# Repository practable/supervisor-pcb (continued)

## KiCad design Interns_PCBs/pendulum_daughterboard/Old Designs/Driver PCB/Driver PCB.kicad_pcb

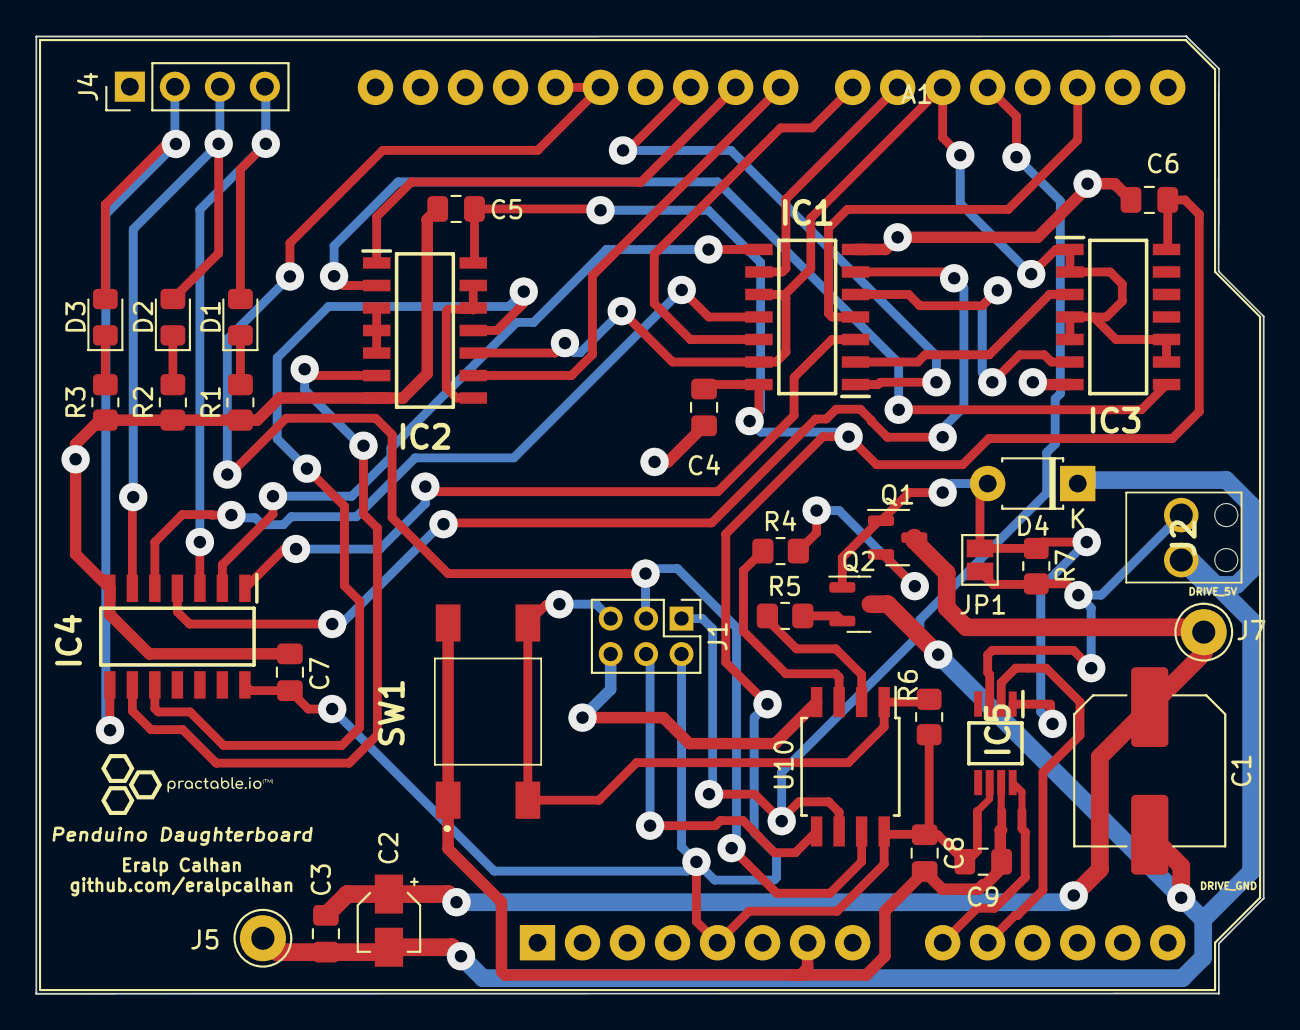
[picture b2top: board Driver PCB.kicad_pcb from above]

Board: 2 copper layers, 69.2 x 54.0 mm, 42 parts (0 on the bottom side), 46 nets.

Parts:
A1: Infineon Motor Shield MOD; Infineon Motor Sheild hiddenPins
C1: 470u; C_Elec_8x10.2
C2: 10u; CP_Elec_3x5.3
C3: 0.1u; C_0805_2012Metric_Pad1.18x1.45mm_HandSolder
C4, C5, C6, C7, C8: 100nF; C_0805_2012Metric_Pad1.18x1.45mm_HandSolder
C9: 0.1uF; C_0805_2012Metric_Pad1.18x1.45mm_HandSolder
D1, D2, D3: LED; LED_0805_2012Metric_Pad1.15x1.40mm_HandSolder
D4: 1N4002; D_T-1_P5.08mm_Horizontal
IC1: AND GATES; SOIC127P600X175-14N
IC2: NAND (Used as AND); SOIC127P600X175-14N
IC3: NAND (Used as Inverter); SOIC127P600X175-14N
IC4: OR; SOIC127P600X175-14N
IC5: MAX9928FAUA+; SOP65P490X110-8N
J1: AVR-ISP-6; PinHeader_2x03_P2.00mm_Vertical
J2: Coil; RSPROPenduinoTerminal
J4: Conn_01x04; PinHeader_1x04_P2.54mm_Vertical
J5: DRIVE_GND; Pin_D1.3mm_L11.0mm
J7: DRIVE_5V_IN; Pin_D1.3mm_L11.0mm
JP1: Shunt Bypass; SolderJumper-2_P1.3mm_Open_Pad1.0x1.5mm
NT1, NT2, NT3, NT4, NT5, NT6: NetTie_2; NetTie-2_SMD_Pad0.5mm
Q1: BC557; SOT-23
Q2: BC547; SOT-23
R1, R2, R3: 120; R_0805_2012Metric_Pad1.20x1.40mm_HandSolder
R4, R5: 2k2; R_0805_2012Metric_Pad1.20x1.40mm_HandSolder
R6: 100k; R_0805_2012Metric_Pad1.20x1.40mm_HandSolder
R7: 10R; R_0805_2012Metric_Pad1.20x1.40mm_HandSolder
SW1: SW_Push; 13019319
U10: ATtiny85-20S; SOIC-8W_5.3x5.3mm_P1.27mm

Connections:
AND_STU_LED_1: IC1.8 (3Y), IC4.2 (B1)
AND_STU_LED_2: IC1.11 (4Y), IC4.5 (B2)
AND_STU_LED_3: IC2.11 (Y4), IC4.10 (B3)
AND_SUP_LED_1: IC1.3 (1Y), IC4.1 (A1)
AND_SUP_LED_2: IC1.6 (2Y), IC4.4 (A2)
AND_SUP_LED_3: IC2.6 (Y2), IC4.9 (A3)
CURRENT_SENSE_OUT: A1.9 (IS_1), NT6.2
CURRENT_SIGN_OUT: A1.10 (IS_2), NT3.1
DRIVE_5V: C1.1, C2.1, C3.1, J7.1, Q1.3 (E)
DRIVE_GND: C1.2, C2.2, C3.2, D4.1 (A), J2.1, J5.1, Q2.3 (E)
DRIVE_INPUT: A1.27 (INH_1), A1.28 (INH_2), J1.3 (SCK), U10.7 (PB2)
DRIVE_MCU: R4.2, U10.3 (XTAL2/PB4)
D_5V: A1.5 (5V), C4.1, C5.1, C6.1, C7.1, C8.1, C9.1, IC1.14 (VCC), IC2.14 (VCC), IC3.14 (VCC), IC4.14 (VCC), J1.2 (VCC), NT1.2, R6.2, U10.8 (VCC)
D_GND: A1.7 (GND), C4.2, C5.2, C6.2, C7.2, C8.2, C9.2, IC1.7 (GND), IC2.7 (GND), IC3.7 (GND), IC4.7 (GND), J1.6 (GND), J4.1, NT2.2, R1.1, R2.1, R3.1, SW1.1, U10.4 (GND)
INV_1: IC1.2 (1B), IC3.3 (Y1)
INV_2: IC1.5 (2B), IC3.6 (Y2)
INV_3: IC2.2 (B1), IC3.8 (Y3)
LOAD_INPUT: A1.19 (D4), J1.1 (MISO), U10.6 (PB1)
LOAD_MCU: R5.2, U10.2 (XTAL1/PB3)
unnamed: D1.1 (K), R1.2
unnamed: D2.1 (K), R2.2
unnamed: D3.1 (K), R3.2
unnamed: D4.2 (K), JP1.1 (A), NT5.1, Q1.1 (C), Q2.1 (C), R7.1
unnamed: IC2.3 (Y1), IC2.4 (A2), IC2.5 (B2)
unnamed: IC2.8 (Y3), IC2.12 (A4), IC2.13 (B4)
unnamed: IC5.1 (RS-), NT5.2
unnamed: IC5.2 (SIGN), NT3.2
unnamed: IC5.3 (RS+), NT4.2
unnamed: IC5.6 (VCC), NT1.1
unnamed: IC5.7 (GND), NT2.1
unnamed: IC5.8 (OUT), NT6.1
unnamed: J1.4 (MOSI), U10.5 (AREF/PB0)
unnamed: J1.5 (~RST), R6.1, SW1.2, U10.1 (~RESET/PB5)
unnamed: J2.2, JP1.2 (B), NT4.1, R7.2
unnamed: Q1.2 (B), R4.1
unnamed: Q2.2 (B), R5.1
OR_OUT_1: D1.2 (A), IC4.3 (Y1), J4.4
OR_OUT_2: D2.2 (A), IC4.6 (Y2), J4.3
OR_OUT_3: D3.2 (A), IC4.8 (Y3), J4.2
STUDENT_ENABLE: A1.20 (D5), IC1.10 (3B), IC1.13 (4B), IC2.10 (B3), IC3.1 (A1), IC3.2 (B1), IC3.4 (A2), IC3.5 (B2), IC3.9 (A3), IC3.10 (B3)
STU_LED_1: A1.21 (D6), IC1.9 (3A)
STU_LED_2: A1.22 (D7), IC1.12 (4A)
STU_LED_3: A1.23 (D8), IC2.9 (A3)
SUP_LED_1: A1.25 (D10), IC1.1 (1A)
SUP_LED_2: A1.17 (D2), IC1.4 (2A)
SUP_LED_3: A1.24 (D9), IC2.1 (A1)

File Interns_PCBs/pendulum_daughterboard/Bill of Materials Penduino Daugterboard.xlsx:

Component Name | Component ID | quantity | Value | Description | Vendor | Part Number | Link | Unit Price (ex. VAT) | Requisition Number | Ordered | Q Boards | Total Price
logic IC AND Gate | IC1 | 1 | NA |  | Farnell | MC74HC08ADG | https://uk.farnell.com/on-semiconductor/mc74hc08adg/ic-74hc-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 | 0.63 |  | No | 42 | 26.46
Logic IC OR Gate | IC2 | 1 | NA |  | Farnell | MC74HC32ADG | https://uk.farnell.com/on-semiconductor/mc74hc32adg/ic-74hc-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 | 0.56999999999999995 |  | No | 42 | 23.939999999999998
Logic IC NAND Gate | IC3 | 1 | NA |  | Farnell | MC74ACT00DG | https://uk.farnell.com/on-semiconductor/mc74act00dg/ic-quad-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 | 0.68 |  | No | 42 | 28.560000000000002
Logic IC NAND Gate | IC4 | 1 | NA |  | Farnell | MC74ACT00DG | https://uk.farnell.com/on-semiconductor/mc74act00dg/ic-quad-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 | 0.68 |  | No | 42 | 28.560000000000002
Current Sense Amplifier | IC5 | 1 | NA | Current Sense Amplifier | Farnell | MAX9928FAUA+ | https://uk.farnell.com/maxim-integrated-products/max9928faua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 | 1.88 |  | Yes | 42 | 78.959999999999994
LED Green | D1 | 1 | NA | Green LED | Farnell | MP008291 | https://uk.farnell.com/multicomp-pro/mp008291/led-green-70mc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 | 0.11 |  | No | 42 | 4.62
LED Orange | D2 | 1 | NA | Orange LED | Farnell | KPT-2012SECK | https://uk.farnell.com/kingbright/kpt-2012seck/led-orange-08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 | 0.12 |  | No | 42 | 5.04
LED Red | D3 | 1 | NA | Red LED | Farnell | MP008293 | https://uk.farnell.com/multicomp-pro/mp008293/led-red-220mcd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 | 0.1 |  | No | 42 | 4.2
Diode | D4 | 1 | NA |  | Farnell | 1N4002 | https://uk.farnell.com/multicomp/1n4002-t/diode-standard-rec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 | 0.13 |  | No | 42 | 5.46
Resistance | R1, R2, R3 | 3 | 120 | 120 OHM resistor for the LED circuit | Farnell | ERA6AEB121V | https://uk.farnell.com/panasonic/era6aeb121v/res-120r-0-125w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 | 0.27 |  | No | 42 | 34.020000000000003
Resistance | R4, R5 | 2 | 2k2 |  | Farnell | 1614917-1 | https://uk.farnell.com/neohm-te-connectivity/1614917-1/res-2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 | 0.17 |  | No | 42 | 14.280000000000001
Resistance | R6 | 1 | 100k |  | Farnell | RS73F2ATTD1003B | https://uk.farnell.com/koa-speer-electronics/rs73f2attd1003b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 | 0.18 |  | No | 42 | 7.56
Resistance | R7 | 1 | 10 |  | Farnell | 2-1614883-3 | https://uk.farnell.com/neohm-te-connectivity/2-1614883-3/res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 | 0.17 |  | No | 42 | 7.1400000000000006
Capacitor | C1 | 1 | 460u |  | Farnell | EEE1CA471UAP | https://uk.farnell.com/panasonic/eee1ca471uap/cap-470-f-16v-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 | 0.69 |  | No | 42 | 28.979999999999997
Capacitor | C2 | 1 | 10u |  | Farnell | AVE106M16A12T-F | https://uk.farnell.com/cornell-dubilier/ave106m16a12t-f/alum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 | 0.45 |  | No | 42 | 18.900000000000002
Capacitor | C3, C4, C5, C6,C7, C8, C9 | 7 | 100nF |  | Farnell | C0805C104K3RACTU | https://uk.farnell.com/kemet/c0805c104k3ractu/cap-0-1-f-25v-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 | 0.06 |  | No | 42 | 17.64
BJT PNP Transistor | Q1 | 1 | NA |  | Farnell | BC807-40LT1G | https://uk.farnell.com/on-semiconductor/bc807-40lt1g/trans-p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 | 0.18 |  | No | 42 | 7.56
BJT NPN Transistor | Q2 | 1 | NA |  | Farnell | BC817,215 | https://uk.farnell.com/nexperia/bc817-215/transistor-npn-45v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 | 0.25 |  | No | 42 | 10.5
AVR Programming Pin | J1 | 1 | NA |  | Farnell | 826925-3 | https://uk.farnell.com/amp-te-connectivity/826925-3/header-t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 | 0.69 |  | No | 42 | 28.979999999999997
2 way PCB terminal | J2 | 1 | NA |  | RS Components | 790-1098 | https://uk.rs-online.com/web/p/pcb-terminal-blocks/7901098 | 0.51200000000000001 |  | No | 42 | 21.504000000000001
4 way PCB terminal | J4 | 1 | NA |  | RS Components | 790-1102 | https://uk.rs-online.com/web/p/pcb-terminal-blocks/7901102 | 0.92400000000000004 |  | No | 42 | 38.808
Tactile Switch | SW1 | 1 | NA | Push Button | Farnell | 1301.9318.24 | https://uk.farnell.com/schurter/1301-9318-24/tactile-switch-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 | 0.42 |  | No | 42 | 17.64
ATtiny85-20S | U1 | 1 | NA | Microcontroller | RS Components | ATTINY85-20SF | https://uk.rs-online.com/web/p/microcontrollers/1717852/?rel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 | 1.8140000000000001 |  | No | 42 | 76.188000000000002
 |  |  |  |  |  |  |  |  |  |  |  | 535.5

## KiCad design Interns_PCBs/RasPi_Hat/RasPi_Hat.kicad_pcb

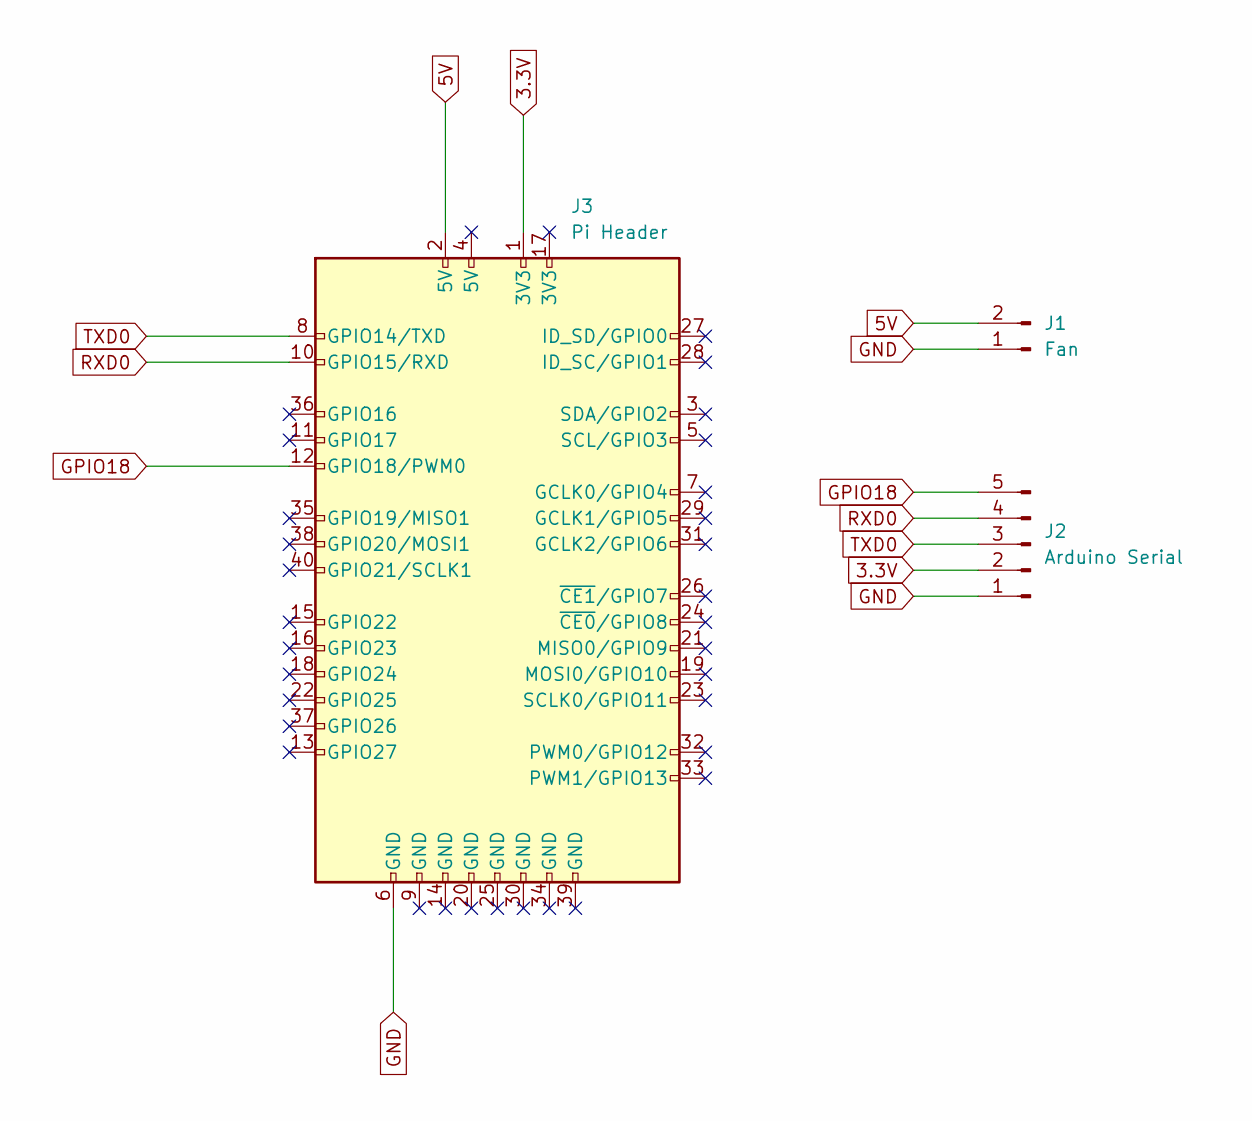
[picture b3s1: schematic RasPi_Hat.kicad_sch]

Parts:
J1: Fan; Molex_KK-254_AE-6410-02A_1x02_P2.54mm_Vertical
J2: Arduino Serial; Molex_KK-254_AE-6410-05A_1x05_P2.54mm_Vertical
J3: Pi Header; PinHeader_2x20_P2.54mm_Vertical

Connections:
3.3V: J2.2, J3.1 (3V3)
5V: J1.2, J3.2 (5V)
GND: J1.1, J2.1, J3.6 (GND)
GPIO18: J2.5, J3.12 (GPIO18/PWM0)
RXD0: J2.4, J3.10 (GPIO15/RXD)
TXD0: J2.3, J3.8 (GPIO14/TXD)

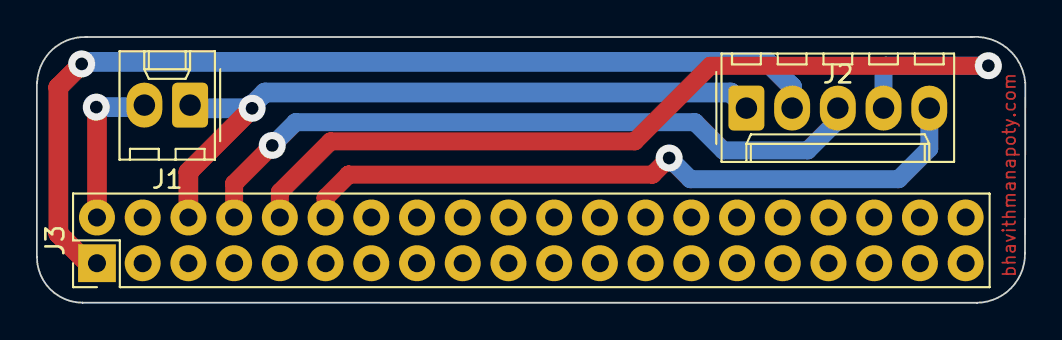
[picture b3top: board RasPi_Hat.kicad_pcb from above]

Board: 2 copper layers, 54.9 x 14.8 mm, 3 parts (0 on the bottom side), 6 nets.

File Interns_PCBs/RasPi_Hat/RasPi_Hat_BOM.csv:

"Id";"Designator";"Package";"Quantity";"Designation";"Supplier and ref";
1;"J2";"Molex_KK-254_AE-6410-05A_1x05_P2.54mm_Vertical";1;"Arduino Serial";;;
2;"J1";"Molex_KK-254_AE-6410-02A_1x02_P2.54mm_Vertical";1;"Fan";;;
3;"J3";"PinHeader_2x20_P2.54mm_Vertical";1;"Pi Header";;;

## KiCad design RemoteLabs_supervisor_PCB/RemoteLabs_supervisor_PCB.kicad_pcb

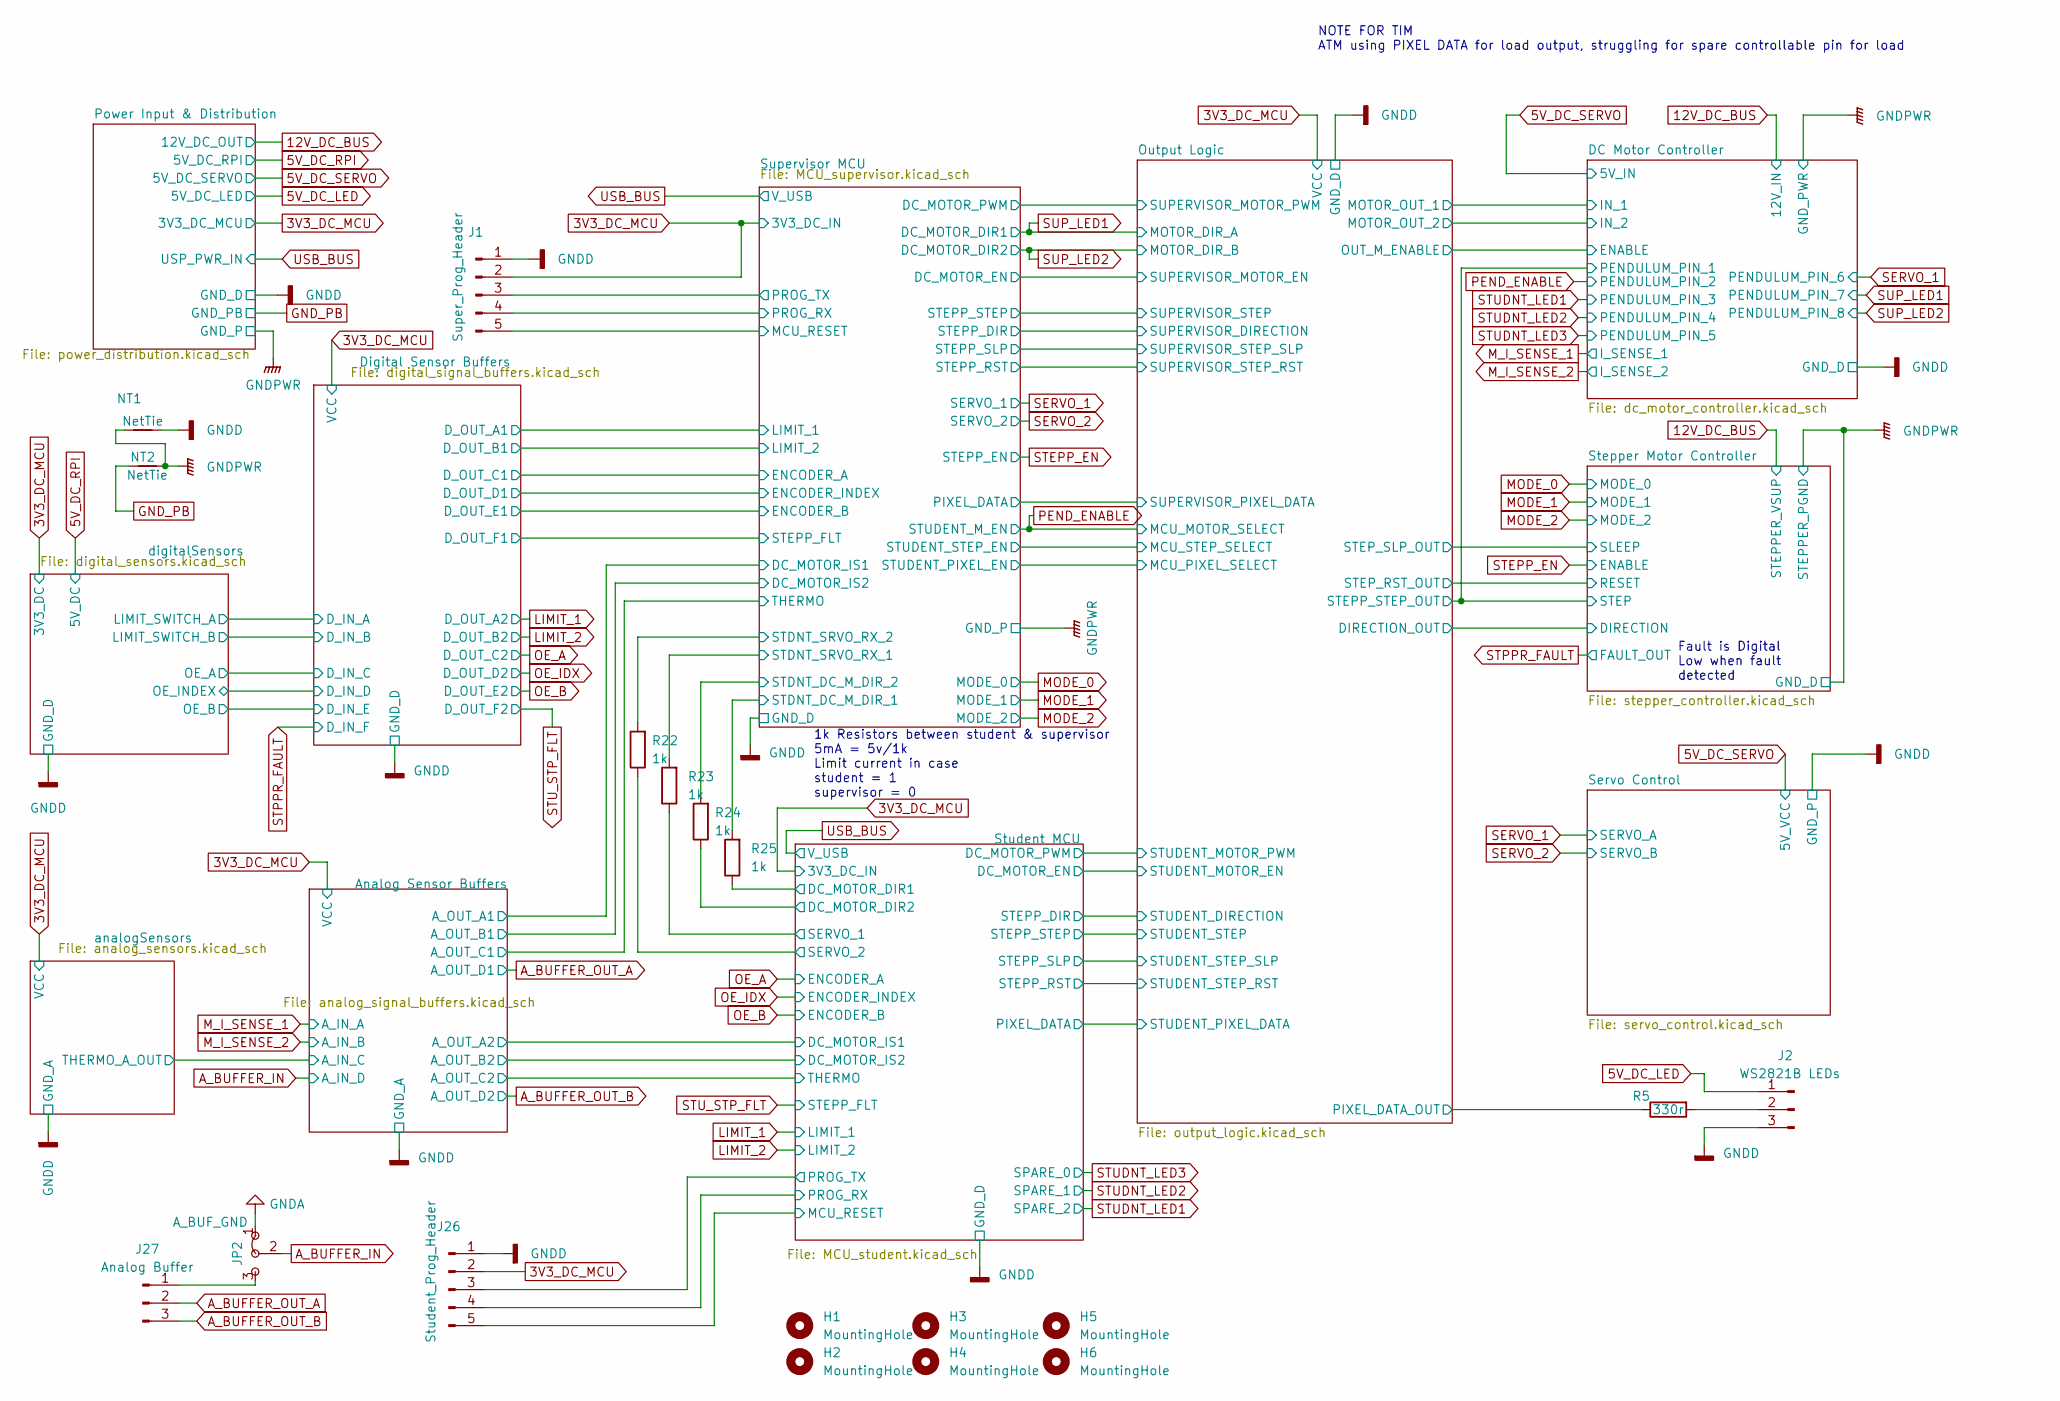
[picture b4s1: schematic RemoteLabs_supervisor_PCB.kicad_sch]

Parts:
H1, H2, H3, H4, H5, H6: MountingHole; MountingHole_3.2mm_M3_Pad_Via
J1: Super_Prog_Header; Molex_KK-254_AE-6410-05A_1x05_P2.54mm_Vertical
J2: WS2821B LEDs; Molex_KK-254_AE-6410-03A_1x03_P2.54mm_Vertical
J26: Student_Prog_Header; Molex_KK-254_AE-6410-05A_1x05_P2.54mm_Vertical
J27: Analog Buffer; PinHeader_1x03_P2.54mm_Vertical
JP2: A_BUF_GND; SolderJumper-3_P1.3mm_Bridged12_RoundedPad1.0x1.5mm
NT1: NetTie; NetTie-2_SMD_Pad2.0mm
NT2: NetTie; NetTie-2_SMD_Pad0.5mm
R5: 330r; R_0805_2012Metric_Pad1.20x1.40mm_HandSolder
R22, R23, R24, R25: 1k; R_0805_2012Metric_Pad1.20x1.40mm_HandSolder

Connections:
3V3_DC_MCU: J1.2, J26.2; also elsewhere on the board
5V_DC_LED: J2.1; also elsewhere on the board
/Output Logic/PIXEL_DATA_OUT: R5.1; also elsewhere on the board
/Student MCU/DC_MOTOR_DIR1: R25.1; also elsewhere on the board
/Student MCU/DC_MOTOR_DIR2: R24.1; also elsewhere on the board
/Student MCU/MCU_RESET: J26.5; also elsewhere on the board
/Student MCU/PROG_RX: J26.4; also elsewhere on the board
/Student MCU/PROG_TX: J26.3; also elsewhere on the board
/Student MCU/SERVO_1: R23.1; also elsewhere on the board
/Student MCU/SERVO_2: R22.1; also elsewhere on the board
/Supervisor MCU/MCU_RESET: J1.5; also elsewhere on the board
/Supervisor MCU/PROG_RX: J1.4; also elsewhere on the board
/Supervisor MCU/PROG_TX: J1.3; also elsewhere on the board
/Supervisor MCU/STDNT_DC_M_DIR_1: R25.2; also elsewhere on the board
/Supervisor MCU/STDNT_DC_M_DIR_2: R24.2; also elsewhere on the board
/Supervisor MCU/STDNT_SRVO_RX_1: R23.2; also elsewhere on the board
/Supervisor MCU/STDNT_SRVO_RX_2: R22.2; also elsewhere on the board
A_BUFFER_IN: JP2.2 (C); also elsewhere on the board
A_BUFFER_OUT_A: J27.2; also elsewhere on the board
A_BUFFER_OUT_B: J27.3; also elsewhere on the board
GNDA: JP2.1 (A)
unnamed: J2.2, R5.2
unnamed: J27.1, JP2.3 (B)

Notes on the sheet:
1k Resistors between student & supervisor 5mA = 5v/1k Limit current in case student = 1 supervisor = 0
Fault is Digital Low when fault detected
NOTE FOR TIM ATM using PIXEL DATA for load output, struggling for spare controllable pin for load

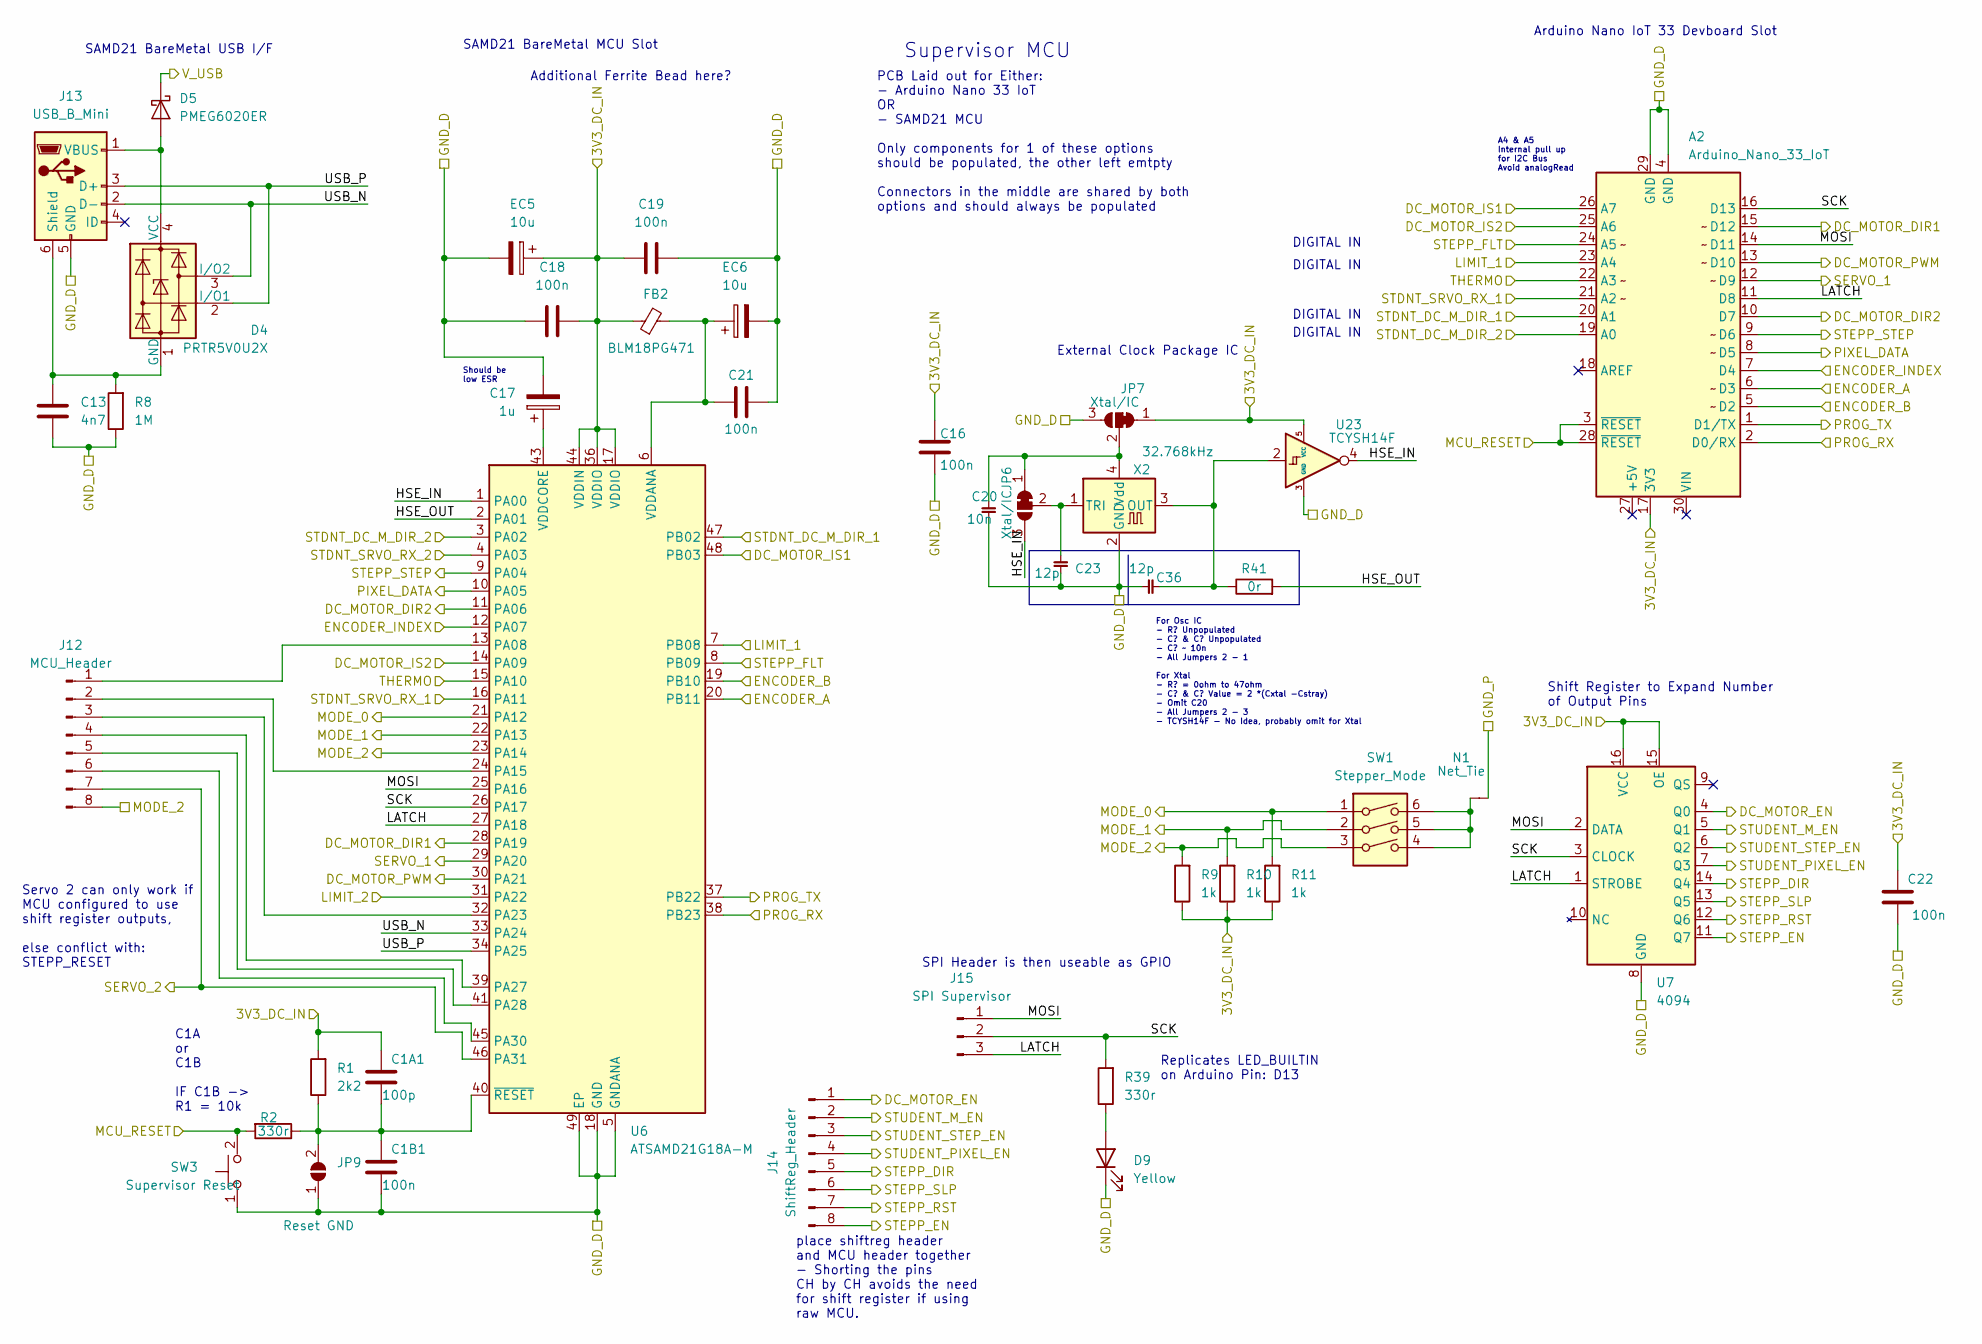
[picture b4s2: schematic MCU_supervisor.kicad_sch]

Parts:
A2: Arduino_Nano_33_IoT; Arduino_Nano
C1A1: 100p; C_0805_2012Metric_Pad1.18x1.45mm_HandSolder
C1B1, C16, C18, C19, C21, C22: 100n; C_0805_2012Metric_Pad1.18x1.45mm_HandSolder
C13: 4n7; C_0805_2012Metric_Pad1.18x1.45mm_HandSolder
C17: 1u; CP_EIA-2012-12_Kemet-R_Pad1.30x1.05mm_HandSolder
C20: 10n; C_0805_2012Metric_Pad1.18x1.45mm_HandSolder
C23, C36: 12p; C_0805_2012Metric_Pad1.18x1.45mm_HandSolder
D4: PRTR5V0U2X; SOT-143
D5: PMEG6020ER; Nexperia_CFP3_SOD-123W
D9: Yellow; D_0805_2012Metric_Pad1.15x1.40mm_HandSolder
EC5, EC6: 10u; CP_Elec_4x5.4
FB2: BLM18PG471; L_0805_2012Metric_Pad1.05x1.20mm_HandSolder
J12: MCU_Header; PinHeader_1x08_P2.54mm_Vertical
J13: USB_B_Mini; USB_Mini-B_Lumberg_2486_01_Horizontal
J14: ShiftReg_Header; PinHeader_1x08_P2.54mm_Vertical
J15: SPI Supervisor; PinHeader_1x03_P2.54mm_Vertical
JP6, JP7: Xtal/IC; SolderJumper-3_P1.3mm_Bridged12_RoundedPad1.0x1.5mm_NumberL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
JP9: Reset GND; SolderJumper-2_P1.3mm_Open_Pad1.0x1.5mm
N1: Net_Tie; NetTie-2_SMD_Pad0.5mm
R1: 2k2; R_0805_2012Metric_Pad1.20x1.40mm_HandSolder
R2, R39: 330r; R_0805_2012Metric_Pad1.20x1.40mm_HandSolder
R8: 1M; R_0805_2012Metric_Pad1.20x1.40mm_HandSolder
R9, R10, R11: 1k; R_0805_2012Metric_Pad1.20x1.40mm_HandSolder
R41: 0r; R_0805_2012Metric_Pad1.20x1.40mm_HandSolder
SW1: Stepper_Mode; SW_DIP_SPSTx03_Slide_6.7x9.18mm_W6.73mm_P2.54mm_LowProfile_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
SW3: Supervisor Reset; SW_Push_1P1T_NO_CK_KSC6xxJ
U6: ATSAMD21G18A-M; QFN-48-1EP_7x7mm_P0.5mm_EP5.15x5.15mm
U7: 4094; SOIC-16_3.9x9.9mm_P1.27mm
U23: TCYSH14F; SOT-23-5_HandSoldering
X2: 32.768kHz; Oscillator_SMD_Abracon_ASE-4Pin_3.2x2.5mm

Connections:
3V3_DC_MCU: A2.17 (3V3), C1A1.1, C16.1, C18.1, C19.2, C22.1, EC5.1, FB2.1, JP7.1 (A), R1.2, R9.1, R10.1, R11.1, U6.17 (VDDIO), U6.36 (VDDIO), U6.44 (VDDIN), U7.15 (OE), U7.16 (VCC), U23.5 (VCC); also elsewhere on the board
/Analog Sensor Buffers/A_OUT_A1: A2.26 (A7), U6.48 (PB03); also elsewhere on the board
/Analog Sensor Buffers/A_OUT_B1: A2.25 (A6), U6.14 (PA09); also elsewhere on the board
/Analog Sensor Buffers/A_OUT_C1: A2.22 (A3), U6.15 (PA10); also elsewhere on the board
/Digital Sensor Buffers/D_OUT_A1: A2.23 (A4), U6.7 (PB08); also elsewhere on the board
/Digital Sensor Buffers/D_OUT_B1: U6.31 (PA22); also elsewhere on the board
/Digital Sensor Buffers/D_OUT_C1: A2.6 (D3), U6.20 (PB11); also elsewhere on the board
/Digital Sensor Buffers/D_OUT_D1: A2.7 (D4), U6.12 (PA07); also elsewhere on the board
/Digital Sensor Buffers/D_OUT_E1: A2.5 (D2), U6.19 (PB10); also elsewhere on the board
/Digital Sensor Buffers/D_OUT_F1: A2.24 (A5), U6.8 (PB09); also elsewhere on the board
/Output Logic/MCU_PIXEL_SELECT: J14.4, U7.7 (Q3); also elsewhere on the board
/Output Logic/MCU_STEP_SELECT: J14.3, U7.6 (Q2); also elsewhere on the board
/Output Logic/SUPERVISOR_DIRECTION: J14.5, U7.14 (Q4); also elsewhere on the board
/Output Logic/SUPERVISOR_MOTOR_EN: J14.1, U7.4 (Q0); also elsewhere on the board
/Output Logic/SUPERVISOR_MOTOR_PWM: A2.13 (D10), U6.30 (PA21); also elsewhere on the board
/Output Logic/SUPERVISOR_PIXEL_DATA: A2.8 (D5), U6.10 (PA05); also elsewhere on the board
/Output Logic/SUPERVISOR_STEP: A2.9 (D6), U6.9 (PA04); also elsewhere on the board
/Output Logic/SUPERVISOR_STEP_RST: J14.7, U7.12 (Q6); also elsewhere on the board
/Output Logic/SUPERVISOR_STEP_SLP: J14.6, U7.13 (Q5); also elsewhere on the board
/Supervisor MCU/HSE_IN: JP6.3 (B), U6.1 (PA00), U23.4
/Supervisor MCU/HSE_OUT: R41.2, U6.2 (PA01)
/Supervisor MCU/LATCH: A2.11 (D8), J15.3, U6.27 (PA18), U7.1 (STROBE)
/Supervisor MCU/MCU_RESET: A2.3 (~RESET), A2.28 (~RESET), R2.2, SW3.2; also elsewhere on the board
/Supervisor MCU/MOSI: A2.14 (D11), J15.1, U6.25 (PA16), U7.2 (DATA)
/Supervisor MCU/PROG_RX: A2.2 (D0/RX), U6.38 (PB23); also elsewhere on the board
/Supervisor MCU/PROG_TX: A2.1 (D1/TX), U6.37 (PB22); also elsewhere on the board
/Supervisor MCU/SCK: A2.16 (D13), J15.2, R39.2, U6.26 (PA17), U7.3 (CLOCK)
/Supervisor MCU/STDNT_DC_M_DIR_1: A2.20 (A1), U6.47 (PB02); also elsewhere on the board
/Supervisor MCU/STDNT_DC_M_DIR_2: A2.19 (A0), U6.3 (PA02); also elsewhere on the board
/Supervisor MCU/STDNT_SRVO_RX_1: A2.21 (A2), U6.16 (PA11); also elsewhere on the board
/Supervisor MCU/STDNT_SRVO_RX_2: U6.4 (PA03); also elsewhere on the board
/Supervisor MCU/USB_N: D4.3 (I/O2), J13.2 (D-), U6.33 (PA24)
/Supervisor MCU/USB_P: D4.2 (I/O1), J13.3 (D+), U6.34 (PA25)
MODE_0: R11.2, SW1.1, U6.21 (PA12); also elsewhere on the board
MODE_1: R10.2, SW1.2, U6.22 (PA13); also elsewhere on the board
MODE_2: J12.8, R9.2, SW1.3, U6.23 (PA14); also elsewhere on the board
unnamed: C1A1.2, C1B1.1, JP9.2 (B), R1.1, R2.1, U6.40 (~RESET)
unnamed: C13.1, D4.1 (GND), J13.6 (Shield), R8.2
unnamed: C17.1, U6.43 (VDDCORE)
unnamed: C20.1, JP6.1 (A), JP7.2 (C), X2.4 (Vdd)
unnamed: C21.2, EC6.1, FB2.2, U6.6 (VDDANA)
unnamed: C23.1, JP6.2 (C), X2.1 (TRI)
unnamed: C36.1, R41.1, U23.2, X2.3 (OUT)
unnamed: D4.4 (VCC), D5.2 (A), J13.1 (VBUS)
unnamed: D9.2 (A), R39.1
unnamed: J12.1, U6.13 (PA08)
unnamed: J12.2, U6.24 (PA15)
unnamed: J12.3, U6.32 (PA23)
unnamed: J12.4, U6.39 (PA27)
unnamed: J12.5, U6.41 (PA28)
unnamed: J12.6, U6.45 (PA30)
unnamed: N1.1 (A), SW1.4, SW1.5, SW1.6
PEND_ENABLE: J14.2, U7.5 (Q1); also elsewhere on the board
SERVO_1: A2.12 (D9), U6.29 (PA20); also elsewhere on the board
SERVO_2: J12.7, U6.46 (PA31); also elsewhere on the board
STEPP_EN: J14.8, U7.11 (Q7); also elsewhere on the board
SUP_LED1: A2.15 (D12), U6.28 (PA19); also elsewhere on the board
SUP_LED2: A2.10 (D7), U6.11 (PA06); also elsewhere on the board
USB_BUS: D5.1 (K); also elsewhere on the board

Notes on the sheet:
PCB Laid out for Either: - Arduino Nano 33 IoT OR - SAMD21 MCU Only components for 1 of these options should be populated, the other left emtpty Connectors in the middle are shared by both options and should always be populated
DIGITAL IN
External Clock Package IC
Should be low ESR
SAMD21 BareMetal USB I/F
Replicates LED_BUILTIN on Arduino Pin: D13
Arduino Nano IoT 33 Devboard Slot
Servo 2 can only work if MCU configured to use shift register outputs, else conflict with: STEPP_RESET
Supervisor MCU
Shift Register to Expand Number of Output Pins
SPI Header is then useable as GPIO
C1A or C1B IF C1B -> R1 = 10k
For Osc IC - R? Unpopulated - C? & C? Unpopulated - C? ~ 10n - All Jumpers 2 - 1 For Xtal - R? = 0ohm to 47ohm - C? & C? Value = 2 *(Cxtal -Cstray) - Omit C20 - All Jumpers 2 - 3 - TCYSH14F - No Idea, probably omit for Xtal
SAMD21 BareMetal MCU Slot
place shiftreg header and MCU header together - Shorting the pins CH by CH avoids the need for shift register if using raw MCU.
A4 & A5 Internal pull up for I2C Bus Avoid analogRead
Additional Ferrite Bead here?

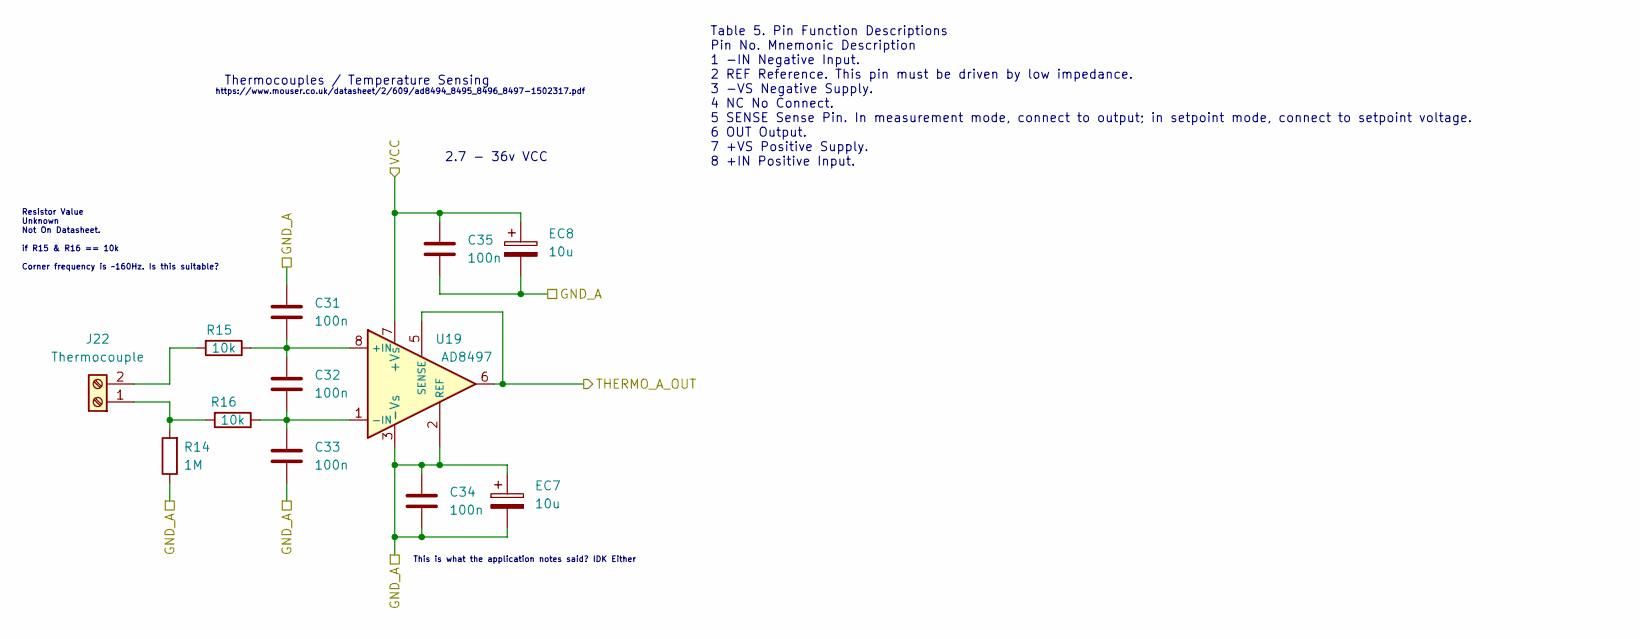
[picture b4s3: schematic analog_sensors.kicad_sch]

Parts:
C31, C32, C33, C34, C35: 100n; C_0805_2012Metric_Pad1.18x1.45mm_HandSolder
EC7, EC8: 10u; CP_Elec_4x5.4
J22: Thermocouple; TerminalBlock_Altech_AK300-2_P5.00mm
R14: 1M; R_0805_2012Metric_Pad1.20x1.40mm_HandSolder
R15, R16: 10k; R_0805_2012Metric_Pad1.20x1.40mm_HandSolder
U19: AD8497; MSOP-8_3x3mm_P0.65mm

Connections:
3V3_DC_MCU: C35.1, EC8.1, U19.7 (+Vs); also elsewhere on the board
/Analog Sensor Buffers/A_IN_C: U19.5 (SENSE), U19.6; also elsewhere on the board
unnamed: C31.2, C32.1, R15.1, U19.8 (+IN)
unnamed: C32.2, C33.1, R16.1, U19.1 (-IN)
unnamed: J22.1, R14.2, R16.2
unnamed: J22.2, R15.2

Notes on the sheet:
Resistor Value Unknown Not On Datasheet. if R15 & R16 == 10k Corner frequency is ~160Hz. Is this suitable?
This is what the application notes said? IDK Either
Table 5. Pin Function Descriptions Pin No. Mnemonic Description 1 −IN Negative Input. 2 REF Reference. This pin must be driven by low impedance. 3 −VS Negative Supply. 4 NC No Connect. 5 SENSE Sense Pin. In measurement mode, connect to output; in setpoint mode, connect to setpoint voltage. 6 OUT Ou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
https://www.mouser.co.uk/datasheet/2/609/ad8494_8495_8496_8497-1502317.pdf
2.7 - 36v VCC
Thermocouples / Temperature Sensing

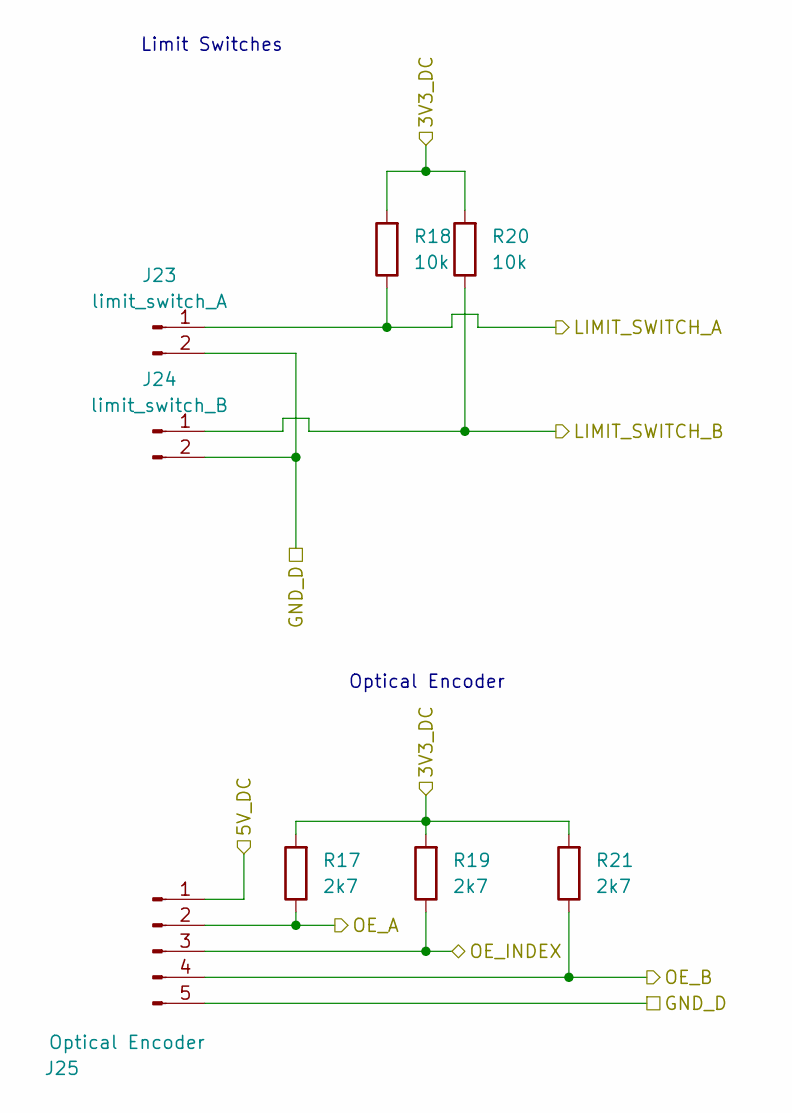
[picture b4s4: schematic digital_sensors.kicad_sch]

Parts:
J23: limit_switch_A; Molex_KK-254_AE-6410-02A_1x02_P2.54mm_Vertical
J24: limit_switch_B; Molex_KK-254_AE-6410-02A_1x02_P2.54mm_Vertical
J25: Optical Encoder; Molex_KK-254_AE-6410-05A_1x05_P2.54mm_Vertical
R17, R19, R21: 2k7; R_0805_2012Metric_Pad1.20x1.40mm_HandSolder
R18, R20: 10k; R_0805_2012Metric_Pad1.20x1.40mm_HandSolder

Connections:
3V3_DC_MCU: R17.2, R18.2, R19.2, R20.2, R21.2; also elsewhere on the board
5V_DC_RPI: J25.1; also elsewhere on the board
/Digital Sensor Buffers/D_IN_A: J23.1, R18.1; also elsewhere on the board
/Digital Sensor Buffers/D_IN_B: J24.1, R20.1; also elsewhere on the board
/Digital Sensor Buffers/D_IN_C: J25.2, R17.1; also elsewhere on the board
/Digital Sensor Buffers/D_IN_D: J25.3, R19.1; also elsewhere on the board
/Digital Sensor Buffers/D_IN_E: J25.4, R21.1; also elsewhere on the board

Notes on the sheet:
Optical Encoder
Limit Switches

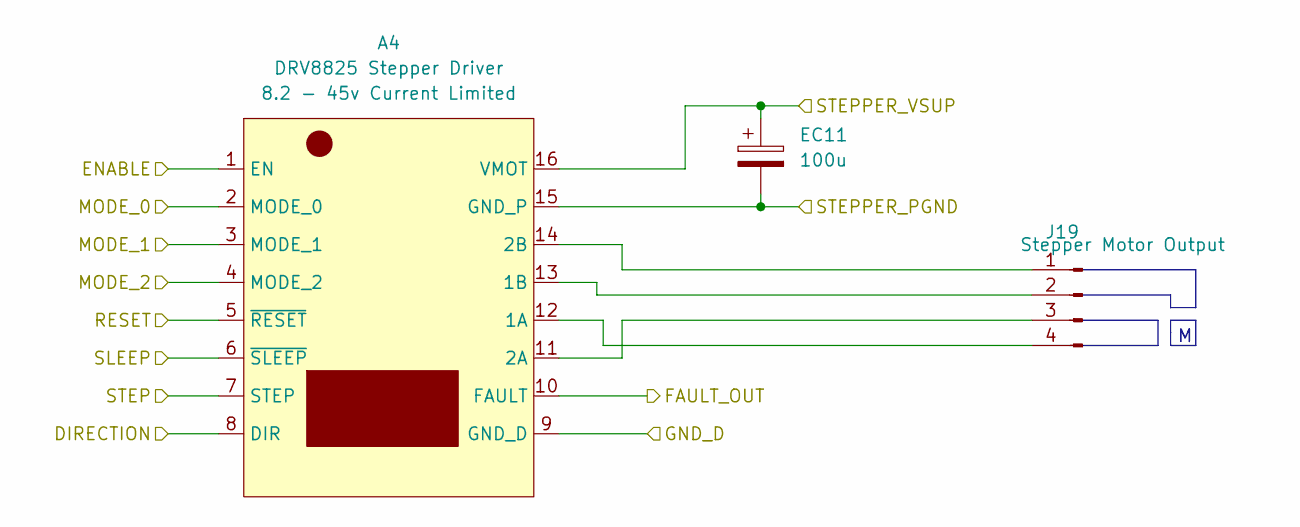
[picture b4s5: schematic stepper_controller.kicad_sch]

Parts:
A4: DRV8825 Stepper Driver; DRV8825 Stepper Motor Module
EC11: 100u; CP_Elec_6.3x7.7
J19: Stepper Motor Output; JST_XH_B4B-XH-A_1x04_P2.50mm_Vertical

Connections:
12V_DC_BUS: A4.16 (VMOT), EC11.1; also elsewhere on the board
/DC Motor Controller/PENDULUM_PIN_1: A4.7 (STEP); also elsewhere on the board
/Output Logic/DIRECTION_OUT: A4.8 (DIR); also elsewhere on the board
/Output Logic/STEP_RST_OUT: A4.5 (~RESET); also elsewhere on the board
/Output Logic/STEP_SLP_OUT: A4.6 (~SLEEP); also elsewhere on the board
MODE_0: A4.2 (MODE_0); also elsewhere on the board
MODE_1: A4.3 (MODE_1); also elsewhere on the board
MODE_2: A4.4 (MODE_2); also elsewhere on the board
unnamed: A4.13 (1B), J19.2
unnamed: A4.14 (2B), J19.1
unnamed: A4.11 (2A), J19.3
unnamed: A4.12 (1A), J19.4
STEPP_EN: A4.1 (EN); also elsewhere on the board
STPPR_FAULT: A4.10 (FAULT); also elsewhere on the board
